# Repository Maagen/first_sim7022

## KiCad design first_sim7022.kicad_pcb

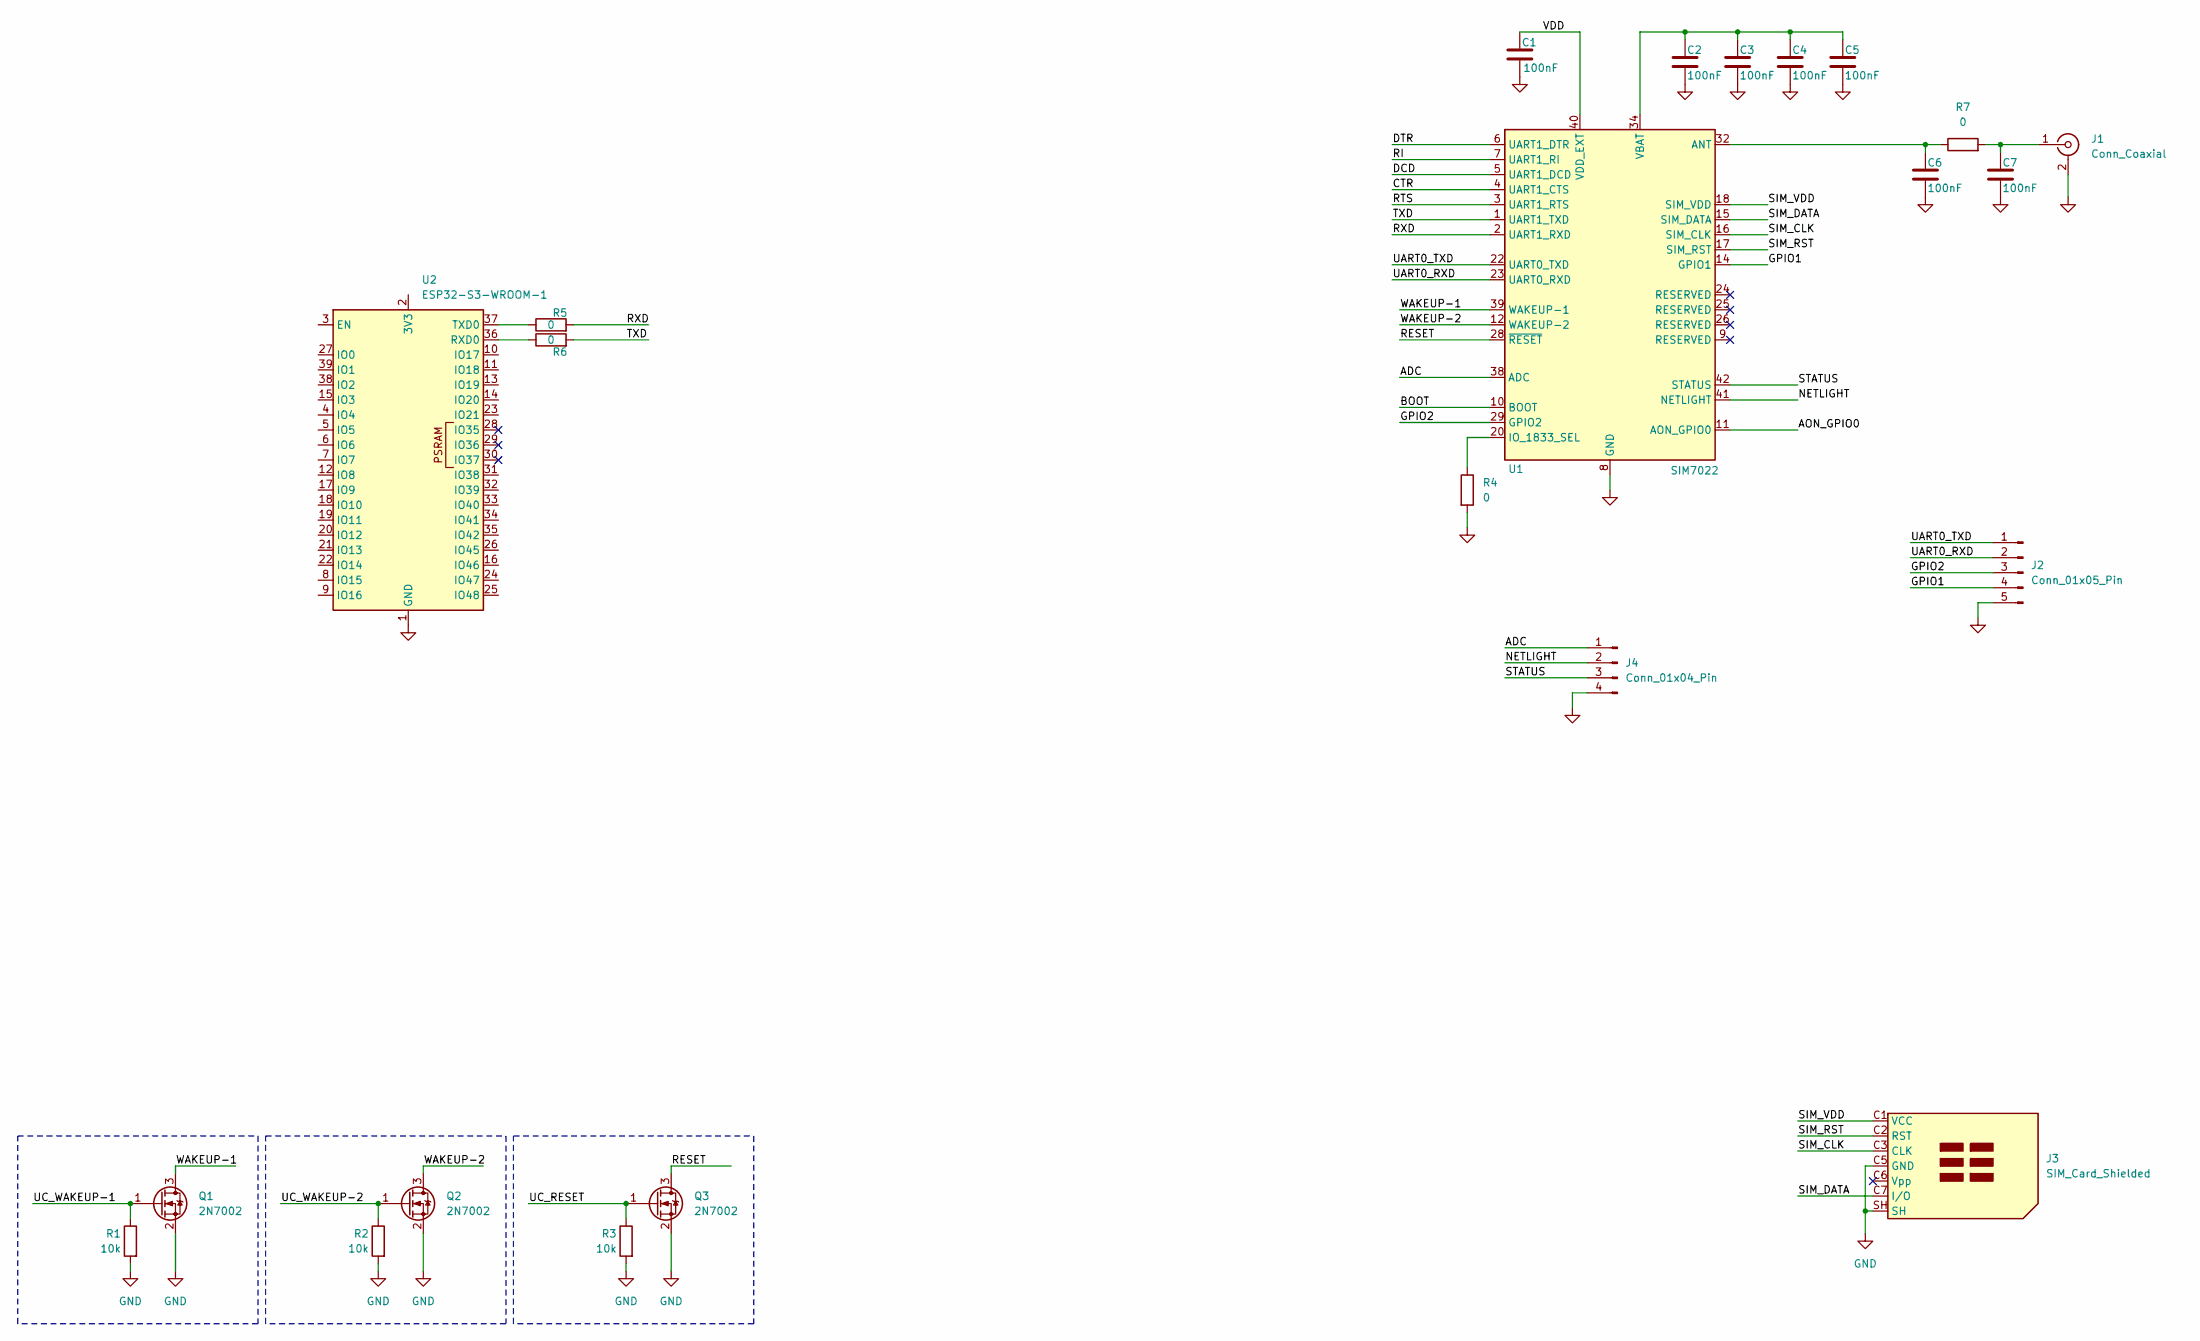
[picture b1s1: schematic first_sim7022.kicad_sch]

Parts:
C1, C2, C3, C4, C5, C6, C7: 100nF; R_0805_2012Metric_Pad1.20x1.40mm_HandSolder
J1: Conn_Coaxial; SMA_Amphenol_901-144_Vertical
J2: Conn_01x05_Pin; PinHeader_1x05_P2.54mm_Vertical
J3: SIM_Card_Shielded; NANO-SIM-SMD_SNO-1330
J4: Conn_01x04_Pin; PinHeader_1x04_P2.54mm_Vertical
Q1, Q2, Q3: 2N7002; SOT-23
R1, R2, R3: 10k; R_0805_2012Metric_Pad1.20x1.40mm_HandSolder
R4, R5, R6, R7: 0; R_0805_2012Metric_Pad1.20x1.40mm_HandSolder
U1: SIM7022; SIMCom_SIM7022
U2: ESP32-S3-WROOM-1

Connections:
/ADC: J4.1, U1.38 (ADC)
/AON_GPIO0: U1.11 (AON_GPIO0)
/BOOT: U1.10 (BOOT)
/CTR: U1.4 (UART1_CTS)
/DCD: U1.5 (UART1_DCD)
/DTR: U1.6 (UART1_DTR)
/GPIO1: J2.4, U1.14 (GPIO1)
/GPIO2: J2.3, U1.29 (GPIO2)
/NETLIGHT: J4.2, U1.41 (NETLIGHT)
/RESET: Q3.3 (D), U1.28 (~RESET)
/RI: U1.7 (UART1_RI)
/RTS: U1.3 (UART1_RTS)
/RXD: R5.2, U1.2 (UART1_RXD)
/SIM_CLK: J3.C3 (CLK), U1.16 (SIM_CLK)
/SIM_DATA: J3.C7 (I/O), U1.15 (SIM_DATA)
/SIM_RST: J3.C2 (RST), U1.17 (SIM_RST)
/SIM_VDD: J3.C1 (VCC), U1.18 (SIM_VDD)
/STATUS: J4.3, U1.42 (STATUS)
/TXD: R6.2, U1.1 (UART1_TXD)
/UART0_RXD: J2.2, U1.23 (UART0_RXD)
/UART0_TXD: J2.1, U1.22 (UART0_TXD)
/UC_RESET: Q3.1 (G), R3.1
/UC_WAKEUP-1: Q1.1 (G), R1.1
/UC_WAKEUP-2: Q2.1 (G), R2.1
/VDD: C1.1, U1.40 (VDD_EXT)
/WAKEUP-1: Q1.3 (D), U1.39 (WAKEUP-1)
/WAKEUP-2: Q2.3 (D), U1.12 (WAKEUP-2)
GND: C1.2, C2.2, C3.2, C4.2, C5.2, C6.2, C7.2, J1.2 (Ext), J2.5, J3.C5 (GND), J3.SH, J4.4, Q1.2 (S), Q2.2 (S), Q3.2 (S), R1.2, R2.2, R3.2, R4.2, U1.8 (GND), U1.13 (GND), U1.19 (GND), U1.21 (GND), U1.27 (GND), U1.30 (GND), U1.31 (GND), U1.33 (GND), U1.36 (GND), U1.37 (GND), U2.1 (GND), U2.40 (GND), U2.41 (GND)
unnamed: C7.1, J1.1 (In), R7.2
unnamed: C6.1, R7.1, U1.32 (ANT)
unnamed: R4.1, U1.20 (IO_1833_SEL)
unnamed: R6.1, U2.36 (RXD0)
unnamed: R5.1, U2.37 (TXD0)
VBAT: C2.1, C3.1, C4.1, C5.1, U1.34 (VBAT), U1.35 (VBAT)

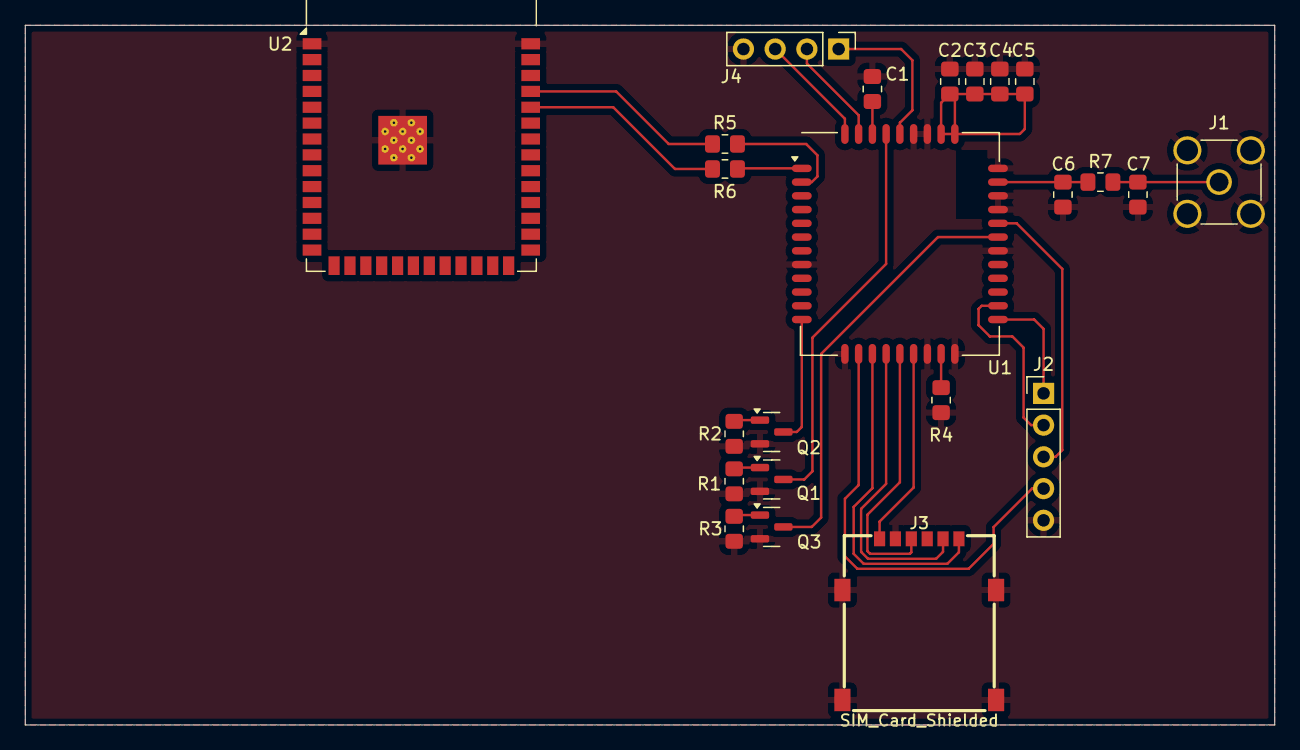
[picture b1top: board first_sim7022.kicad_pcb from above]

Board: 2 copper layers, 100.0 x 56.0 mm, 23 parts (0 on the bottom side), 27 nets.

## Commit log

2024-03-05 gitignore added
2024-03-05 remove backups
